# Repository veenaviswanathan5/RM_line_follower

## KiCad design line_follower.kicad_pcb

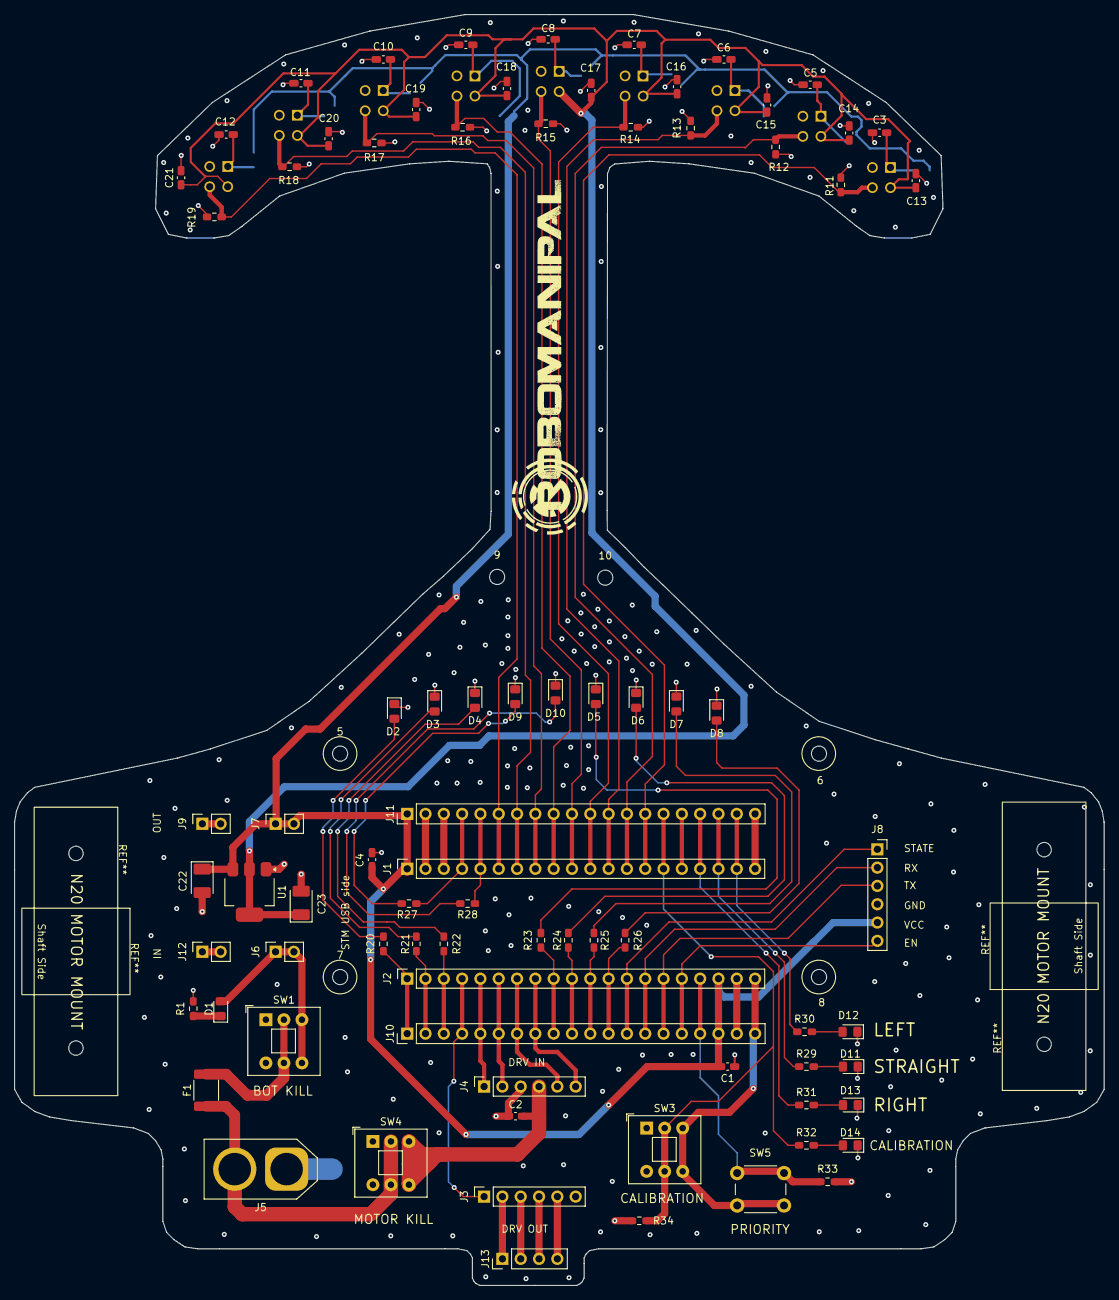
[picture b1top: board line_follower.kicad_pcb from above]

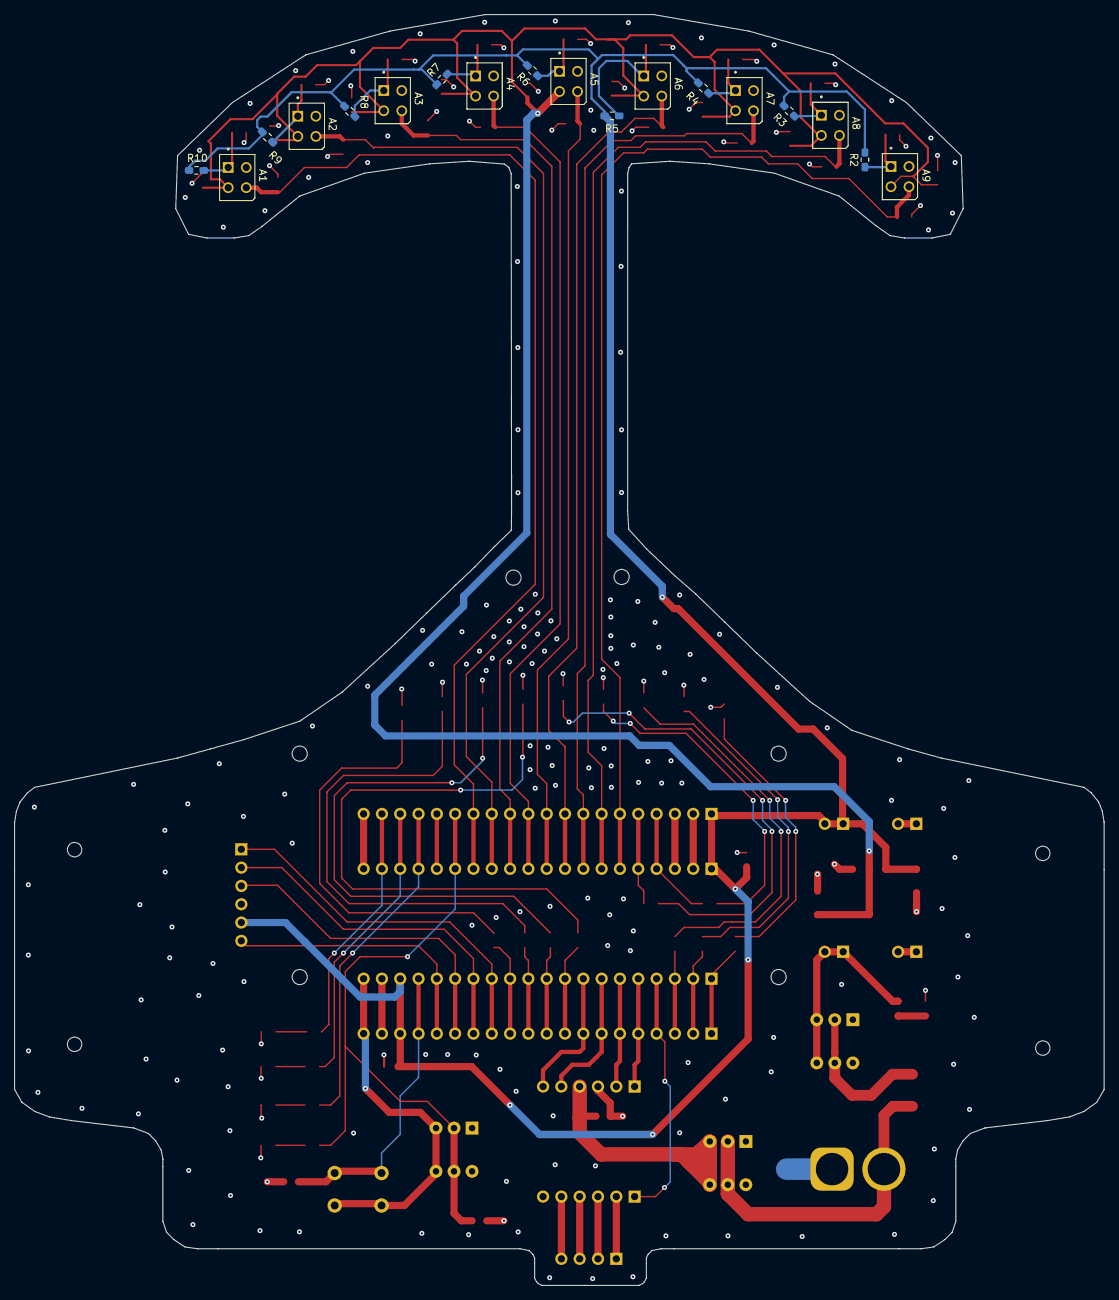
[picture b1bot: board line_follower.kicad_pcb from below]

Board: 2 copper layers, 151.1 x 176.3 mm, 105 parts (18 on the bottom side), 70 nets.

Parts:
5, 6, 7, 8, 9, 10: MountingHole_2.1mm
A1, A2, A3, A4, A5, A6, A7, A8, A9: RPR-220; PHODET_RPR-220
C1, C2, C3, C4, C5, C6, C7, C8, C9, C10, C11, C12, C13, C14, C15, C16, C17, C18, C19, C20, C21: 0.1u; C_0603_1608Metric_Pad1.08x0.95mm_HandSolder
C22, C23: 22uf; CP_EIA-3528-12_Kemet-T_HandSolder
D1, D2, D3, D4, D5, D6, D7, D8, D9, D10, D11, D12, D13, D14: LED; LED_0805_2012Metric_Pad1.15x1.40mm_HandSolder
F1: Polyfuse; R_1812_4532Metric_Pad1.30x3.40mm_HandSolder
J1, J2: Conn_01x20_Socket; PinSocket_1x20_P2.54mm_Vertical
J3, J4, J8: Conn_01x06_Socket; PinSocket_1x06_P2.54mm_Vertical
J5: XT60-M; AMASS_XT60-M_1x02_P7.20mm_Vertical
J6, J7, J9, J12: Conn_01x02_Socket; PinSocket_1x02_P2.54mm_Vertical
J10, J11: Conn_01x20_Pin; PinHeader_1x20_P2.54mm_Vertical
J13: Conn_01x04_Pin; PinHeader_1x04_P2.54mm_Vertical
R1: R; R_0603_1608Metric_Pad0.98x0.95mm_HandSolder
R2, R3, R4, R5, R6, R7, R8, R9, R10: 220; R_0603_1608Metric_Pad0.98x0.95mm_HandSolder
R11, R12, R13, R14, R15, R16, R17, R18, R19: 47k; R_0603_1608Metric_Pad0.98x0.95mm_HandSolder
R20, R21, R22, R23, R24, R25, R26, R27, R28, R29, R30, R31, R32: 150; R_0603_1608Metric_Pad0.98x0.95mm_HandSolder
R33, R34: 10k; R_0603_1608Metric_Pad0.98x0.95mm_HandSolder
SW1, SW3, SW4: SW_Push_DPDT; SW_Push_2P2T_Toggle_CK_PVA2xxH3xxxxxxV2
SW5: SW_Push; SW_PUSH_6mm_H5mm
U1: AMS1117-3.3; SOT-223-3_TabPin2

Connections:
/3.3V_LDO: A1.4, A2.4, A3.4, A4.4, A5.4, A6.4, A7.4, A8.4, A9.4, C13.1, C14.1, C15.1, C16.1, C17.1, C18.1, C19.1, C20.1, C21.1, C23.1, U1.2 (VO)
/3.3V_STM: J1.3, J11.3
/3.3V_STM_1: J2.20, J10.20, SW3.3 (C), SW3.6 (C), SW5.1
/5V_STM: C1.2, C4.2, C22.1, J1.1, J2.18, J7.1, J7.2, J8.5, J10.18, J11.1, R2.1, R3.1, R4.1, R5.1, R6.1, R7.1, R8.1, R9.1, R10.1, U1.3 (VI)
/BUCK_IN: D1.2 (A), J6.1, J6.2, SW1.3 (C), SW1.6 (C)
/CALIB: J1.15, J11.15, R32.1, R34.2, SW3.2 (B), SW3.5 (B)
/EEP: J2.4, J3.1, J10.4
/EN: J2.16, J8.6, J10.16
/FUSE_OUT: F1.2, SW1.2 (B), SW1.5 (B)
/IN1: J2.5, J4.1, J10.5
/IN2: J2.6, J4.2, J10.6
/IN3: J2.7, J4.5, J10.7
/IN4: J2.8, J4.6, J10.8
/LEFT: J1.19, J11.19, R30.1
/NRST: J1.16, J11.16
/OUT1: J3.2, J13.1
/OUT2: J3.3, J13.2
/OUT3: J3.4, J13.3
/OUT4: J3.5, J13.4
/PA1: A1.3, J1.14, J11.14, R11.2
/PA2: A2.3, J1.13, J11.13, R12.2
/PA3: A3.3, J1.12, J11.12, R13.2
/PA4: A4.3, J1.11, J11.11, R14.2
/PA5: A5.3, J1.10, J11.10, R15.2
/PA6: A6.3, J1.9, J11.9, R16.2
/PA7: A7.3, J1.8, J11.8, R17.2
/PA12: J2.9, J10.9, R23.2
/PA15: J2.10, J10.10, R24.2
/PB0: A8.3, J1.7, J11.7, R18.2
/PB1: A9.3, J1.6, J11.6, R19.2
/PB2: J1.5, J11.5, R28.2
/PB3: J2.11, J10.11, R25.2
/PB4: J2.12, J10.12, R26.2
/PB5: J2.13, J8.1, J10.13
/PB6: J2.14, J8.2, J10.14
/PB7: J2.15, J8.3, J10.15
/PB9: J2.17, J10.17, R33.1, SW5.2
/PB10: J1.4, J11.4, R27.2
/PB12: J2.1, J10.1, R20.2
/PB13: J2.2, J10.2, R21.2
/PB14: J2.3, J10.3, R22.2
/PC14: J1.18, J11.18, R29.1
/PC15: J1.17, J11.17, R31.1
/RPR_ANO_1: A9.1, C12.1, R2.2
/RPR_ANO_2: A8.1, C11.1, R3.2
/RPR_ANO_3: A7.1, C10.1, R4.2
/RPR_ANO_4: A6.1, C9.1, R5.2
/RPR_ANO_5: A5.1, C8.1, R6.2
/RPR_ANO_6: A4.1, C7.1, R7.2
/RPR_ANO_7: A3.1, C6.1, R8.2
/RPR_ANO_8: A2.1, C5.1, R9.2
/RPR_ANO_9: A1.1, C3.1, R10.2
/VBAT_STM: J1.20, J11.20
/VCC_DRV: C2.2, J4.4, SW4.3 (C), SW4.6 (C)
/pow_led-: D1.1 (K), R1.1
BAT+: F1.1, J5.2, SW4.2 (B), SW4.5 (B)
GND: A1.2, A2.2, A3.2, A4.2, A5.2, A6.2, A7.2, A8.2, A9.2, C1.1, C2.1, C3.2, C4.1, C5.2, C6.2, C7.2, C8.2, C9.2, C10.2, C11.2, C12.2, C13.2, C14.2, C15.2, C16.2, C17.2, C18.2, C19.2, C20.2, C21.2, C22.2, C23.2, D2.1 (K), D3.1 (K), D4.1 (K), D5.1 (K), D6.1 (K), D7.1 (K), D8.1 (K), D9.1 (K), D10.1 (K), D11.1 (K), D12.1 (K), D13.1 (K), D14.1 (K), J1.2, J2.19, J4.3, J5.1, J8.4, J9.1, J9.2, J10.19, J11.2, J12.1, J12.2, R1.2, R11.1, R12.1, R13.1, R14.1, R15.1, R16.1, R17.1, R18.1, R19.1, R33.2, R34.1, U1.1 (GND)
unnamed: D2.2 (A), R20.1
unnamed: D3.2 (A), R21.1
unnamed: D4.2 (A), R22.1
unnamed: D5.2 (A), R23.1
unnamed: D6.2 (A), R24.1
unnamed: D7.2 (A), R25.1
unnamed: D8.2 (A), R26.1
unnamed: D9.2 (A), R27.1
unnamed: D10.2 (A), R28.1
unnamed: D11.2 (A), R29.2
unnamed: D12.2 (A), R30.2
unnamed: D13.2 (A), R31.2
unnamed: D14.2 (A), R32.2

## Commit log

2025-06-02 Add KiCad project files
2025-06-05 schematic updated by veena
2025-06-10 minor changes
2025-06-11 assigned footprints
2025-06-12 schematic complete
2025-06-13 Add .lck file to version control
2025-06-13 Remove auto_saved_files
2025-06-13 some placement done
2025-06-13 some placement
2025-06-14 placement done
2025-06-16 Add back backup zip files
2025-06-16 minor design errors left
2025-06-17 changed to emitter resistor
2025-06-17 pcb finished
2025-06-18 all drc errors fixed
2025-06-18 battery mount holes placed, pcb complete
2025-06-18 pcb complete
2025-06-18 added logo
2025-06-21 final pcb
2025-06-25 new schematic complete
